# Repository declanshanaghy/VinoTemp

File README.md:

Controller Board for VinoTemp wine fridge to allow it to function as a beer fridge :-D

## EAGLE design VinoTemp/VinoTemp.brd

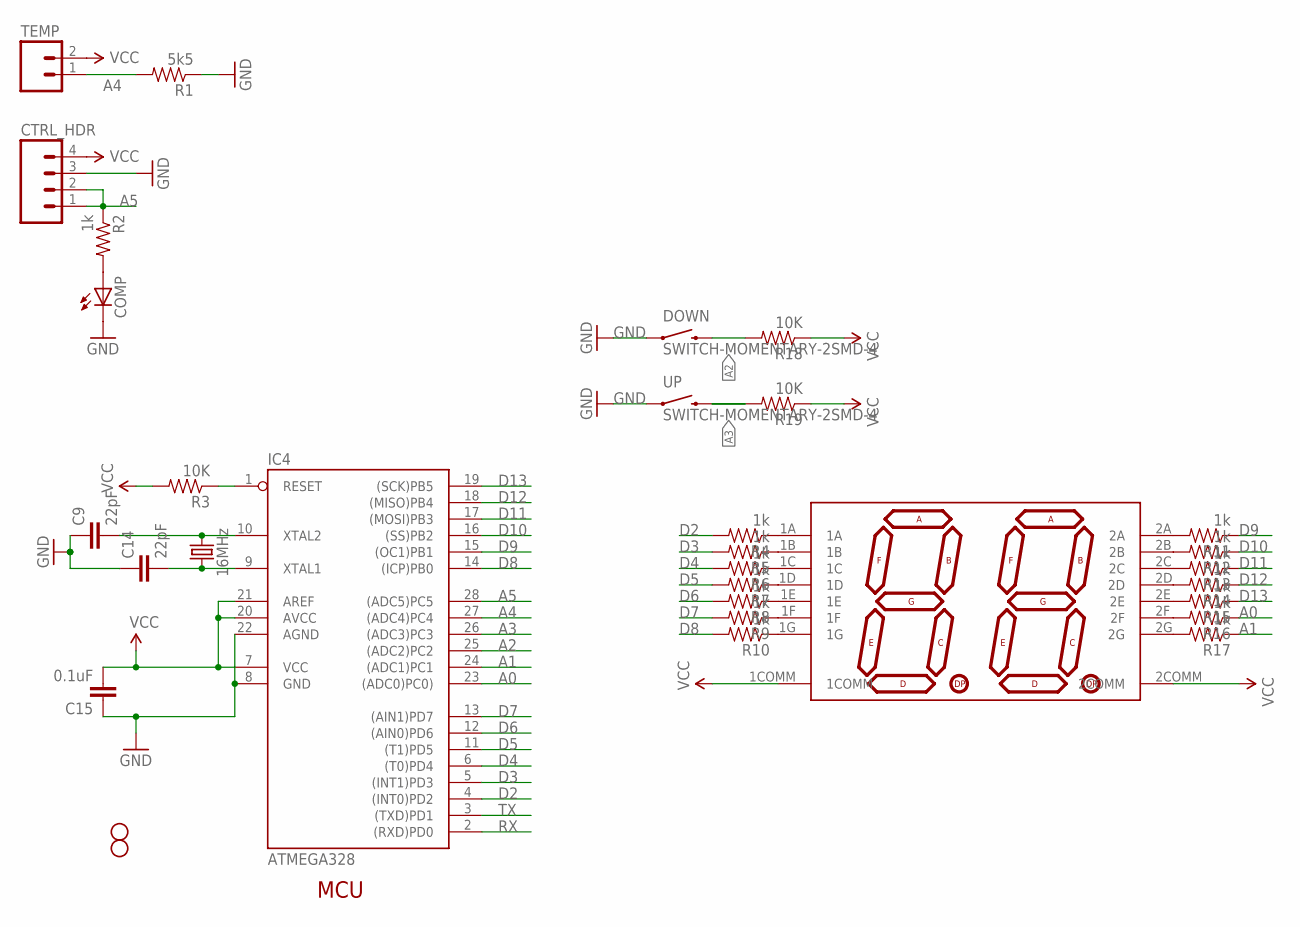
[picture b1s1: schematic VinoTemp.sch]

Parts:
C9, C14: 22pF; CAP-PTH-SMALL2
C15: 0.1uF; CAP-PTH-SMALL2
COMP: LED3MM
CTRL_HDR: M04POLAR; MOLEX-1X4
DOWN: SWITCH-MOMENTARY-2SMD-4; TACTILE_SWITCH_TALL
IC4: ATMEGA328; DIL28-3
JP2, JP6: STAND-OFF#2; STAND-OFF-#2
R1: 5k5; AXIAL-0.3
R2, R4, R5, R6, R7, R8, R9, R10, R11, R12, R13, R14, R15, R16, R17: 1k; 0805
R3, R18, R19: 10K; 0805
TEMP: M02POLAR; MOLEX-1X2
U$1: 7-SEGMENT-DISPLAY-2-DIGITPTH; 7-SEGMENT-DISPLAY-2-DIGIT-KINGBRIGHT-DA04
UP: SWITCH-MOMENTARY-2SMD-4; TACTILE_SWITCH_TALL
Y1: 16MHz; HC49US

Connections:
A0: IC4.23 ((ADC0)PC0)), R16.1
A1: IC4.24 ((ADC1)PC1), R17.1
A2: DOWN.B2 (2), IC4.25 ((ADC2)PC2), R18.2
A3: IC4.26 ((ADC3)PC3), R19.2, UP.B2 (2)
A4: IC4.27 ((ADC4)PC4), R1.P$2 (2), TEMP.1
A5: CTRL_HDR.1, CTRL_HDR.2, IC4.28 ((ADC5)PC5), R2.1
D2: IC4.4 ((INT0)PD2), R4.2
D3: IC4.5 ((INT1)PD3), R5.2
D4: IC4.6 ((T0)PD4), R6.2
D5: IC4.11 ((T1)PD5), R7.2
D6: IC4.12 ((AIN0)PD6), R8.2
D7: IC4.13 ((AIN1)PD7), R9.2
D8: IC4.14 ((ICP)PB0), R10.2
D9: IC4.15 ((OC1)PB1), R11.1
D10: IC4.16 ((SS)PB2), R12.1
D11: IC4.17 ((MOSI)PB3), R13.1
D12: IC4.18 ((MISO)PB4), R14.1
D13: IC4.19 ((SCK)PB5), R15.1
GND: C9.1, C14.1, C15.1, COMP.K (C), CTRL_HDR.3, DOWN.A2 (1), IC4.8 (GND), IC4.22 (AGND), R1.P$1 (1), UP.A2 (1)
unnamed: COMP.A, R2.2
unnamed: R4.1, U$1.1A
unnamed: R5.1, U$1.1B
unnamed: R6.1, U$1.1C
unnamed: R7.1, U$1.1D
unnamed: R8.1, U$1.1E
unnamed: R9.1, U$1.1F
unnamed: R10.1, U$1.1G
unnamed: R11.2, U$1.2A
unnamed: R12.2, U$1.2B
unnamed: R13.2, U$1.2C
unnamed: R14.2, U$1.2D
unnamed: R15.2, U$1.2E
unnamed: R16.2, U$1.2F
unnamed: R17.2, U$1.2G
RST: IC4.1 (RESET), R3.1
RX: IC4.2 ((RXD)PD0)
TX: IC4.3 ((TXD)PD1)
VCC: C15.2, CTRL_HDR.4, IC4.7 (VCC), IC4.20 (AVCC), IC4.21 (AREF), R3.2, R18.1, R19.1, TEMP.2, U$1.1COMM, U$1.2COMM
XTAL1: C14.2, IC4.9 (XTAL1), Y1.1
XTAL2: C9.2, IC4.10 (XTAL2), Y1.2

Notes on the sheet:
MCU

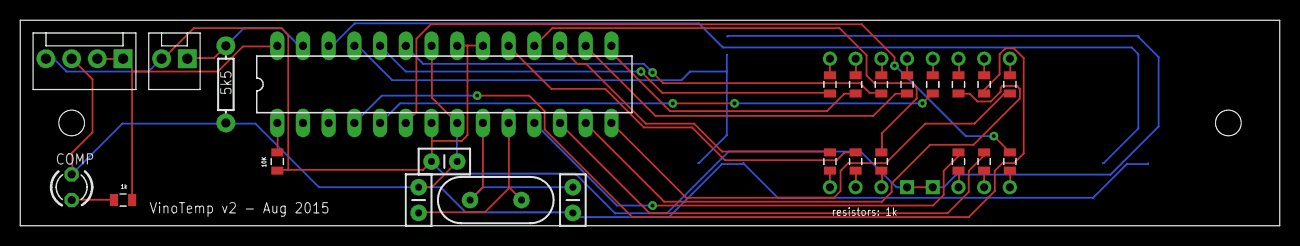
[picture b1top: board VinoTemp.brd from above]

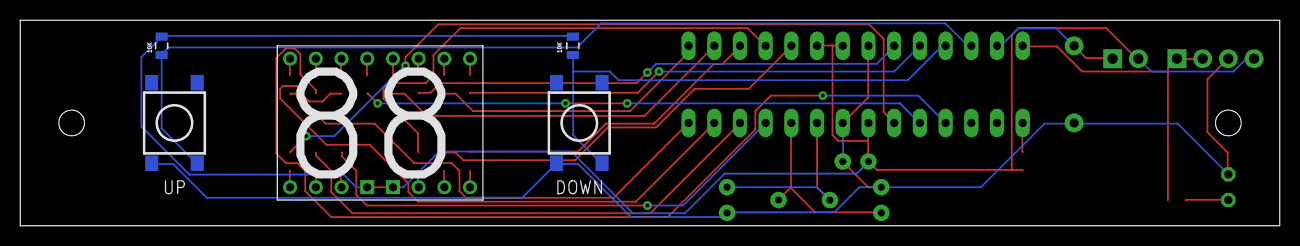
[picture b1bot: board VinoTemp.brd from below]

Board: 2 copper layers, 124.5 x 20.3 mm, 32 parts (5 on the bottom side), 38 nets.

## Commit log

2015-06-30 Added double press to enter setting mode
2015-07-07 V1 board submitted to OSH Park
2015-08-03 Modified code to work with upside down characters
2015-08-08 Fixed upside down LCD display

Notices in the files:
parts and their libraries:
SparkFun-Electromechanical: Licensing: Creative Commons ShareAlike 4.0 International - https://creativecommons.org/licenses/by-sa/4.0
